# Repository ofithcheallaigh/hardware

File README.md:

# hardware
This is a location where I intend to keep any hardware designs I am working on.

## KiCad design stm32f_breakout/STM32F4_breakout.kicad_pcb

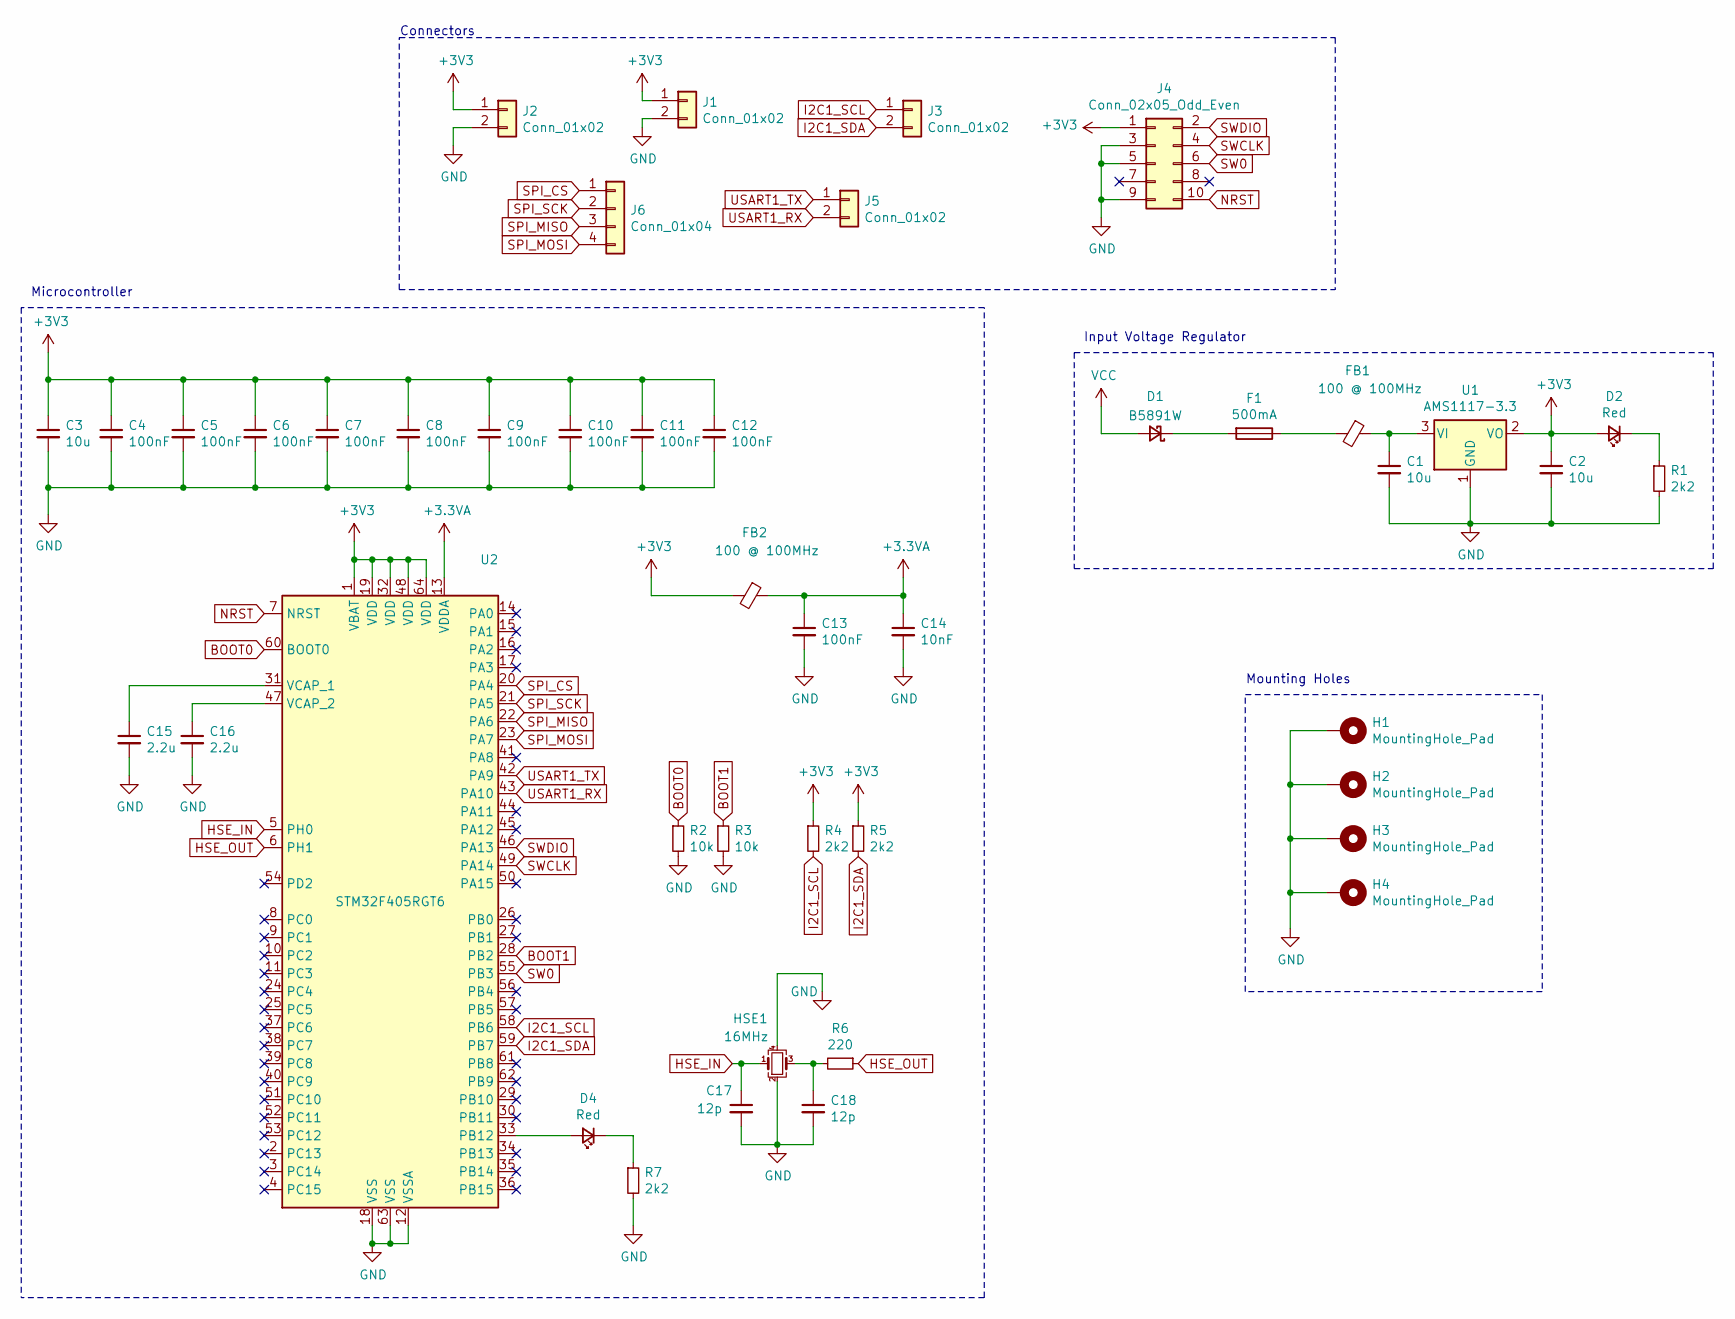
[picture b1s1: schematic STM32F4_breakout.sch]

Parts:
C1, C2: 10u; C_0805_2012Metric
C3: 10u; C_0603_1608Metric
C4, C5, C6, C7, C8, C9, C10, C11, C12, C13: 100nF; C_0402_1005Metric
C14: 10nF; C_0402_1005Metric
C15, C16: 2.2u; C_0603_1608Metric
C17, C18: 12p; C_0402_1005Metric
D1: B5891W; D_SOD-123
D2, D4: Red; LED_0603_1608Metric
F1: 500mA; Fuse_0603_1608Metric
FB1, FB2: 100 @ 100MHz; L_0805_2012Metric
H1, H2, H3, H4: MountingHole_Pad; MountingHole_4.3mm_M4_Pad_Via
HSE1: 16MHz; Crystal_SMD_3225-4Pin_3.2x2.5mm
J1, J2, J3, J5: Conn_01x02; PinHeader_1x02_P2.54mm_Vertical
J4: Conn_02x05_Odd_Even; PinHeader_2x05_P1.27mm_Vertical
J6: Conn_01x04; PinHeader_1x04_P2.54mm_Vertical
R1, R7: 2k2; R_0603_1608Metric
R2, R3: 10k; R_0402_1005Metric
R4, R5: 2k2; R_0402_1005Metric
R6: 220; R_0402_1005Metric
U1: AMS1117-3.3; SOT-223-3_TabPin2
U2: STM32F405RGT6; LQFP-64_10x10mm_P0.5mm

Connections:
+3.3VA: C13.1, C14.1, FB2.1, U2.13 (VDDA)
+3V3: C2.1, C3.1, C4.1, C5.1, C6.1, C7.1, C8.1, C9.1, C10.1, C11.1, C12.1, D2.2 (A), FB2.2, J1.1, J2.1, J4.1, R4.1, R5.1, U1.2 (VO), U2.1 (VBAT), U2.19 (VDD), U2.32 (VDD), U2.48 (VDD), U2.64 (VDD)
BOOT0: R2.1, U2.60 (BOOT0)
BOOT1: R3.1, U2.28 (PB2)
GND: C1.2, C2.2, C3.2, C4.2, C5.2, C6.2, C7.2, C8.2, C9.2, C10.2, C11.2, C12.2, C13.2, C14.2, C15.2, C16.2, C17.2, C18.2, H1.1, H2.1, H3.1, H4.1, HSE1.2, HSE1.4, J1.2, J2.2, J4.3, J4.5, J4.9, R1.2, R2.2, R3.2, R7.2, U1.1 (GND), U2.12 (VSSA), U2.18 (VSS), U2.63 (VSS)
HSE_IN: C17.1, HSE1.1, U2.5 (PH0)
HSE_OUT: R6.1, U2.6 (PH1)
I2C1_SCL: J3.1, R4.2, U2.58 (PB6)
I2C1_SDA: J3.2, R5.2, U2.59 (PB7)
NRST: J4.10, U2.7 (NRST)
unnamed: C1.1, FB1.1, U1.3 (VI)
unnamed: C15.1, U2.31 (VCAP_1)
unnamed: C16.1, U2.47 (VCAP_2)
unnamed: C18.1, HSE1.3, R6.2
unnamed: D1.1 (K), F1.2
unnamed: D2.1 (K), R1.1
unnamed: D4.1 (K), R7.1
unnamed: D4.2 (A), U2.33 (PB12)
unnamed: F1.1, FB1.2
SPI_CS: J6.1, U2.20 (PA4)
SPI_MISO: J6.3, U2.22 (PA6)
SPI_MOSI: J6.4, U2.23 (PA7)
SPI_SCK: J6.2, U2.21 (PA5)
SW0: J4.6, U2.55 (PB3)
SWCLK: J4.4, U2.49 (PA14)
SWDIO: J4.2, U2.46 (PA13)
USART1_RX: J5.2, U2.43 (PA10)
USART1_TX: J5.1, U2.42 (PA9)
VCC: D1.2 (A)

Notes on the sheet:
Input Voltage Regulator
Microcontroller
Connectors
Mounting Holes

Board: 2 copper layers, 44 parts (0 on the bottom side), 28 nets, no tracks yet.

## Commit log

2020-07-26 STM32F UART SPI I2C breakout board
